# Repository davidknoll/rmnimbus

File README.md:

Projects and tools I've made while tinkering with the RM Nimbus PC-186 & PC-386
===============================================================================

Unless otherwise stated, anything here that was made by me can be used/distributed/etc under the MIT license, and none of it is approved or endorsed by [RM plc](https://www.rm.com/).

* ***8087repro*** - Reproduction of the 8087 option board for the PC-186, using a DS1100 delay line IC instead of EP8274. Prototype PCB passes basic testing.
* ***idecf*** - Ideas for how to attach a CF card to the PC-386, which uses the MCA bus so the right hardware can be harder to find.
* ***joysticksplitter*** - Allows two Atari/Commodore joysticks to be connected, as mentioned in sections 2.5.5 and 2.16.4 of the Service Manual. Two buttons are supported per joystick on pins 6 and 9, with power on pin 7. Not yet built/tested.
* ***nimbuscd*** - This contains some experiments with using a SCSI CD-ROM drive (initially, emulated with BlueSCSI) on the PC-186 with original DCB. I'm hoping to make it into `nimbuscd.sys`, a CD-ROM device driver to use with MSCDEX.
* ***nimbusmouse*** - I saw [this PS/2 mouse adaptor](https://www.thenimbus.co.uk/upgrades-and-maintenance/ps2mouse) and thought it could be done with a smaller microcontroller (specifically, an ATtiny2313 using [ATTinyCore](https://github.com/SpenceKonde/ATTinyCore)).
  * My version isn't working at the moment, but I've had aspects of it working. Work in progress.
* ***nimbusrtc*** - Attach a DS12C887A RTC pretty much directly to the bus as an expansion card.
  * This and similar RTCs are made for a multiplexed bus, so no extra latches and buffers are necessary. But because the Nimbus I/O bus is just half of a 16-bit bus, it only sees accesses where A0 is 0. The bus is shifted by one bit to make sure A0 can be 0 and the RTC registers can all still be accessed. The shift is reversed in software.
  * Not all of the RTC's RAM is accessible due to the available address space in one slot. Only chip selects 0, 2 and 4 can be used, as we also need to make sure A7 is 0 to address the right half of the RTC. Chip select 0 and interrupt 0 are generally reserved for the disk controller. An interrupt is unnecessary for the RTC if only using simple get/set commands.
  * There is a device driver that can be loaded from CONFIG.SYS to use the RTC on startup and with the TIME and DATE commands.
  * Alternatively, the get/set commands provided can be compiled on the Nimbus itself using Microsoft QuickC under SETPC. They default to expecting the RTC in slot 4, but this can be set with a switch ```/0``` - ```/4```.
* ***PC-386 RAM*** - Incomplete attempts at reproducing a decent size memory module for the PC-386.
* ***Piconet transceiver*** - Facilitates connecting a microcontroller to Piconet. Prototype PCBs so far untested- suspected pinout problem.
* ***piexpansion*** - Put a Raspberry Pi Pico W with an SD card on the PC-186 expansion bus, to hopefully emulate any physical expansion card, even the disk controller. Prototype PCB passes basic testing.
* ***reink*** - Generate block 0 for SCSI disks of any geometry, so you're not restricted to the few models in HDFORM.
  * This doesn't write the sector to the disk itself, as I don't have access to the system programmer's manual that would probably tell me how to do that. The sector is written to stdout instead, and you'll need to write it to the disk separately. (Which is made a whole lot simpler if using a SCSI2SD.)
  * You then need to run STAMP and/or HARDDISK on the Nimbus to partition the disk. I found a 64MB limit on DOS partition size, with only one DOS partition supported per disk.
  * This is not a replacement for an actual low-level format if you need one.
* ***simmadaptor*** - Adaptors for 30 or 72 pin SIMMs on the 186. Not yet tested, prototype PCBs ordered.
* ***ymplay*** - Play YM chiptune audio files using the AY-3-8910 in the Nimbus.

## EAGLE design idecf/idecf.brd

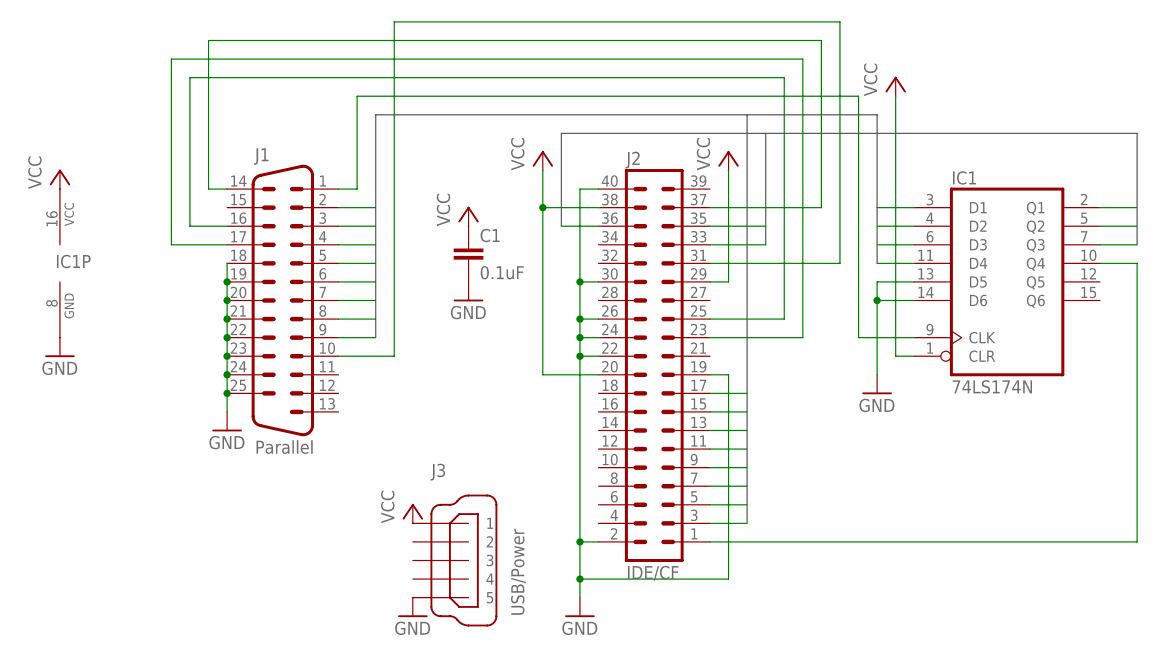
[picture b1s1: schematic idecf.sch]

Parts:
C1: 0.1uF; C050-024X044
IC1: 74LS174N; DIL16
J1: Parallel; M25HP
J2: IDE/CF; MA20-2W
J3: USB/Power; 32005-201

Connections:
!CS0: J1.14, J2.37
!RD: J1.16, J2.25
!RESET: IC1.10 (Q4), J2.1
!WR: J1.17, J2.23
A0: IC1.2 (Q1), J2.35
A1: IC1.5 (Q2), J2.33
A2: IC1.7 (Q3), J2.36
ALE: IC1.9 (CLK), J1.1
D0: IC1.3 (D1), J1.2, J2.17
D1: IC1.4 (D2), J1.3, J2.15
D2: IC1.6 (D3), J1.4, J2.13
D3: IC1.11 (D4), J1.5, J2.11
D4: J1.6, J2.9
D5: J1.7, J2.7
D6: J1.8, J2.5
D7: J1.9, J2.3
GND: C1.2, IC1.8 (GND), IC1.13 (D5), IC1.14 (D6), J1.18, J1.19, J1.20, J1.21, J1.22, J1.23, J1.24, J1.25, J2.2, J2.19, J2.22, J2.24, J2.26, J2.30, J2.40, J3.5
IRQ: J1.10, J2.31
VCC: C1.1, IC1.1 (CLR), IC1.16 (VCC), J2.20, J2.29, J2.38, J3.1

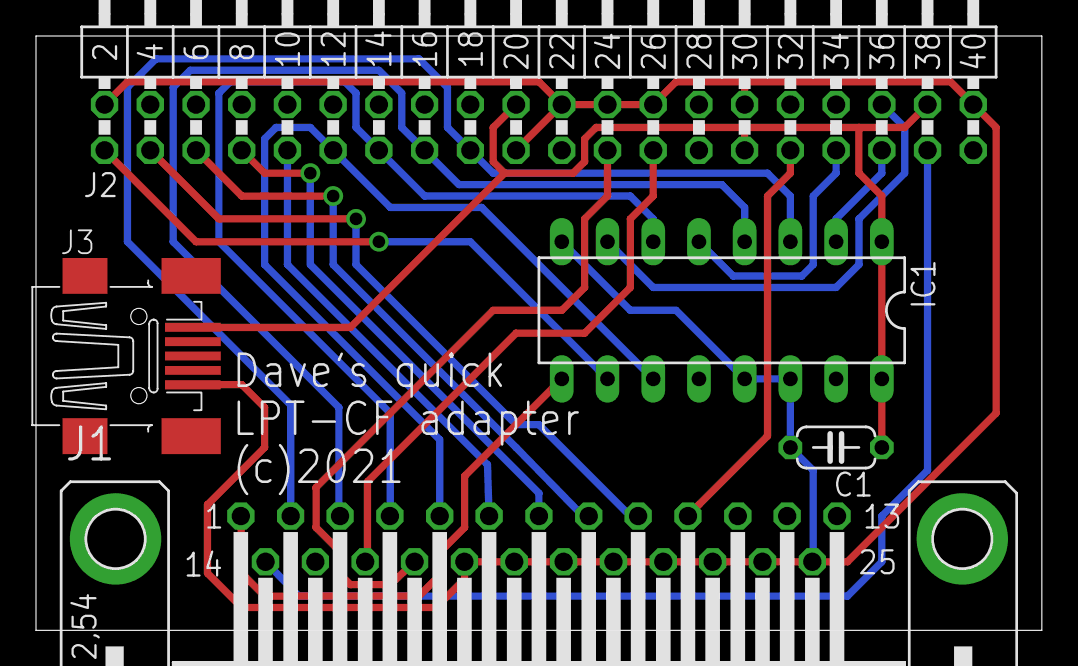
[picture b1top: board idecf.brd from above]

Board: 2 copper layers, 55.9 x 33.0 mm, 5 parts (0 on the bottom side), 19 nets.

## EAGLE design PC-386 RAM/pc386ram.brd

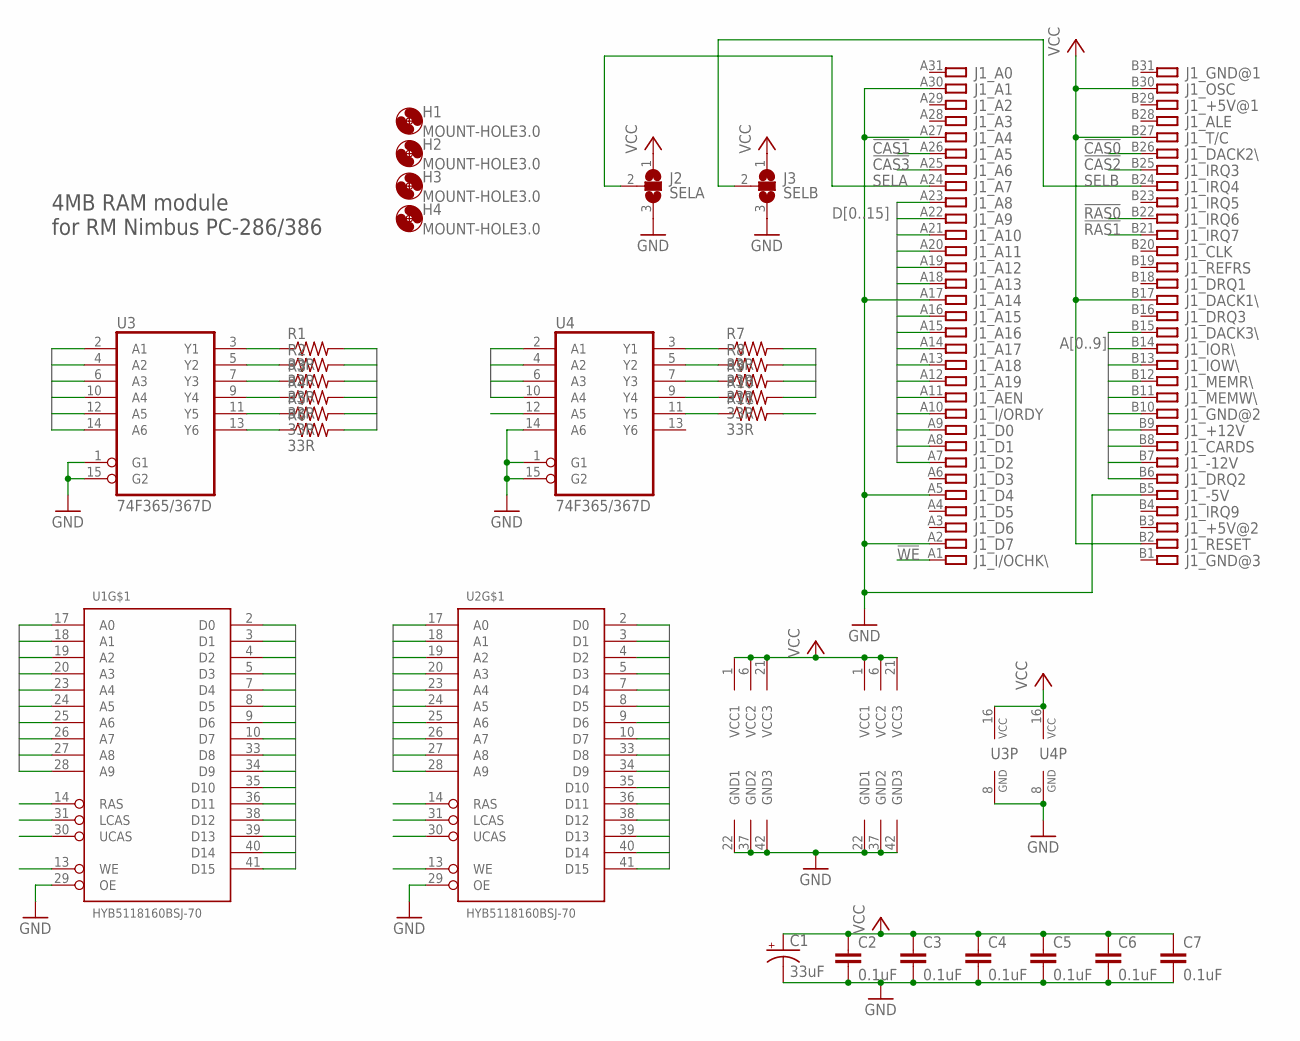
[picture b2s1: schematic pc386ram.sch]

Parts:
C1: 33uF; E2,5-7
C2, C3, C4, C5, C6, C7: 0.1uF; C050-024X044
H1, H2, H3, H4: MOUNT-HOLE3.0; 3,0
J1: PC-386 RAM slot; IBM8BIT
J2: SELA; SJ_2
J3: SELB; SJ_2
R1, R2, R3, R4, R5, R6, R7, R8, R9, R10, R11: 33R; 0204/7
U1, U2: HYB5118160BSJ-70; SOJ-42
U3, U4: 74F365/367D; SO16

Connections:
!CAS0: J1.B26, U1.30 (UCAS)
!CAS1: J1.A26, U1.31 (LCAS)
!CAS2: J1.B25, U2.30 (UCAS)
!CAS3: J1.A25, U2.31 (LCAS)
!RAS0: J1.B22, U1.14 (RAS)
!RAS1: J1.B21, U2.14 (RAS)
!WE: J1.A1, U4.12 (A5)
A0: J1.B6, U3.2 (A1)
A1: J1.B7, U3.4 (A2)
A2: J1.B8, U3.6 (A3)
A3: J1.B9, U3.10 (A4)
A4: J1.B10, U3.12 (A5)
A5: J1.B11, U3.14 (A6)
A6: J1.B12, U4.2 (A1)
A7: J1.B13, U4.4 (A2)
A8: J1.B14, U4.6 (A3)
A9: J1.B15, U4.10 (A4)
B!WE: R11.1, U4.11 (Y5)
BA0: R1.1, U3.3 (Y1)
BA1: R2.1, U3.5 (Y2)
BA2: R3.1, U3.7 (Y3)
BA3: R4.1, U3.9 (Y4)
BA4: R5.1, U3.11 (Y5)
BA5: R6.1, U3.13 (Y6)
BA6: R7.1, U4.3 (Y1)
BA7: R8.1, U4.5 (Y2)
BA8: R9.1, U4.7 (Y3)
BA9: R10.1, U4.9 (Y4)
D0: J1.A7, U1.2 (D0), U2.2 (D0)
D1: J1.A8, U1.3 (D1), U2.3 (D1)
D2: J1.A9, U1.4 (D2), U2.4 (D2)
D3: J1.A10, U1.5 (D3), U2.5 (D3)
D4: J1.A11, U1.7 (D4), U2.7 (D4)
D5: J1.A12, U1.8 (D5), U2.8 (D5)
D6: J1.A13, U1.9 (D6), U2.9 (D6)
D7: J1.A14, U1.10 (D7), U2.10 (D7)
D8: J1.A15, U1.33 (D8), U2.33 (D8)
D9: J1.A16, U1.34 (D9), U2.34 (D9)
D10: J1.A18, U1.35 (D10), U2.35 (D10)
D11: J1.A19, U1.36 (D11), U2.36 (D11)
D12: J1.A20, U1.38 (D12), U2.38 (D12)
D13: J1.A21, U1.39 (D13), U2.39 (D13)
D14: J1.A22, U1.40 (D14), U2.40 (D14)
D15: J1.A23, U1.41 (D15), U2.41 (D15)
GND: C1.-, C2.2, C3.2, C4.2, C5.2, C6.2, C7.2, J1.A2, J1.A5, J1.A17, J1.A27, J1.A30, J1.B5, J2.3, J3.3, U1.22 (GND1), U1.29 (OE), U1.37 (GND2), U1.42 (GND3), U2.22 (GND1), U2.29 (OE), U2.37 (GND2), U2.42 (GND3), U3.1 (G1), U3.8 (GND), U3.15 (G2), U4.1 (G1), U4.8 (GND), U4.14 (A6), U4.15 (G2)
M!WE: R11.2, U1.13 (WE), U2.13 (WE)
MA0: R1.2, U1.17 (A0), U2.17 (A0)
MA1: R2.2, U1.18 (A1), U2.18 (A1)
MA2: R3.2, U1.19 (A2), U2.19 (A2)
MA3: R4.2, U1.20 (A3), U2.20 (A3)
MA4: R5.2, U1.23 (A4), U2.23 (A4)
MA5: R6.2, U1.24 (A5), U2.24 (A5)
MA6: R7.2, U1.25 (A6), U2.25 (A6)
MA7: R8.2, U1.26 (A7), U2.26 (A7)
MA8: R9.2, U1.27 (A8), U2.27 (A8)
MA9: R10.2, U1.28 (A9), U2.28 (A9)
SELA: J1.A24, J2.2
SELB: J1.B24, J3.2
VCC: C1.+, C2.1, C3.1, C4.1, C5.1, C6.1, C7.1, J1.B2, J1.B17, J1.B27, J1.B30, J2.1, J3.1, U1.1 (VCC1), U1.6 (VCC2), U1.21 (VCC3), U2.1 (VCC1), U2.6 (VCC2), U2.21 (VCC3), U3.16 (VCC), U4.16 (VCC)

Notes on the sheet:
4MB RAM module for RM Nimbus PC-286/386

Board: 2 copper layers, 29 parts (0 on the bottom side), 59 nets, no tracks yet.

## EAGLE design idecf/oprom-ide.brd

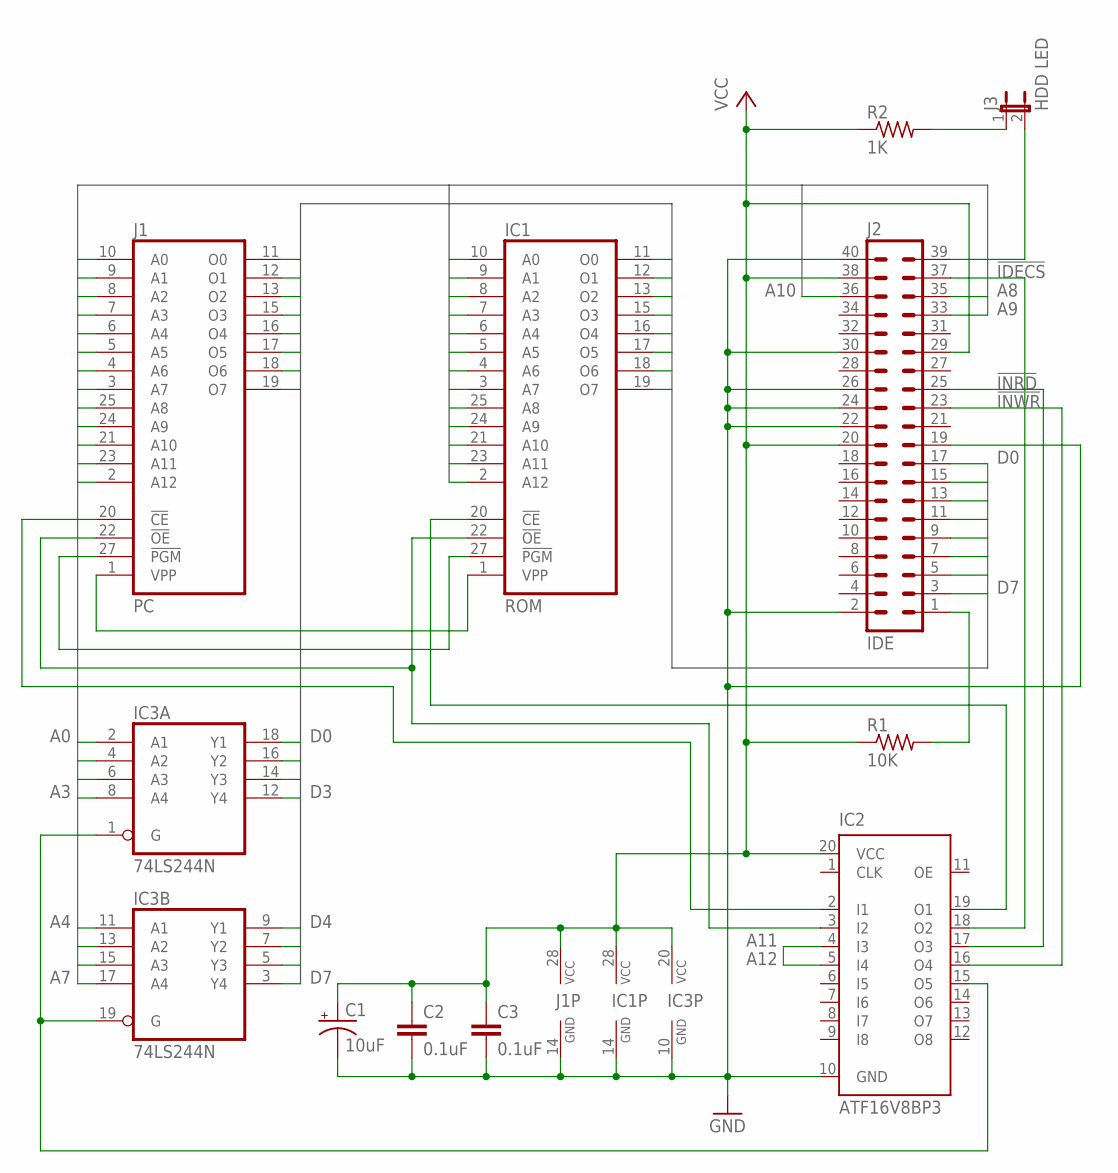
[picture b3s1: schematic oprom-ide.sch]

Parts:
C1: 10uF; E2,5-6
C2, C3: 0.1uF; C050-024X044
IC1: ROM; DIL28
IC2: ATF16V8BP3; DIL20
IC3: 74LS244N; DIL20
J1: PC; DIL28
J2: IDE; MA20-2W
J3: HDD LED; JP1
R1: 10K; 0204/7
R2: 1K; 0204/7

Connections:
!ATOD: IC2.15 (O5), IC3.1 (G), IC3.19 (G)
!EXCS: IC2.2 (I1), J1.20 (!CE)
!EXRD: IC1.22 (!OE), IC2.3 (I2), J1.22 (!OE)
!EXWR: IC1.27 (!PGM), J1.27 (!PGM)
!IDECS: IC2.18 (O2), J2.37
!IDELED: J2.39, J3.2
!INRD: IC2.17 (O3), J2.25
!INWR: IC2.16 (O4), J2.23
!RESET: J2.1, R1.2
!ROMCS: IC1.20 (!CE), IC2.19 (O1)
A0: IC1.10 (A0), IC3.2 (A1), J1.10 (A0)
A1: IC1.9 (A1), IC3.4 (A2), J1.9 (A1)
A2: IC1.8 (A2), IC3.6 (A3), J1.8 (A2)
A3: IC1.7 (A3), IC3.8 (A4), J1.7 (A3)
A4: IC1.6 (A4), IC3.11 (A1), J1.6 (A4)
A5: IC1.5 (A5), IC3.13 (A2), J1.5 (A5)
A6: IC1.4 (A6), IC3.15 (A3), J1.4 (A6)
A7: IC1.3 (A7), IC3.17 (A4), J1.3 (A7)
A8: IC1.25 (A8), J1.25 (A8), J2.35
A9: IC1.24 (A9), J1.24 (A9), J2.33
A10: IC1.21 (A10), J1.21 (A10), J2.36
A11: IC1.23 (A11), IC2.4 (I3), J1.23 (A11)
A12: IC1.2 (A12), IC2.5 (I4), J1.2 (A12)
D0: IC1.11 (O0), IC3.18 (Y1), J1.11 (O0), J2.17
D1: IC1.12 (O1), IC3.16 (Y2), J1.12 (O1), J2.15
D2: IC1.13 (O2), IC3.14 (Y3), J1.13 (O2), J2.13
D3: IC1.15 (O3), IC3.12 (Y4), J1.15 (O3), J2.11
D4: IC1.16 (O4), IC3.9 (Y1), J1.16 (O4), J2.9
D5: IC1.17 (O5), IC3.7 (Y2), J1.17 (O5), J2.7
D6: IC1.18 (O6), IC3.5 (Y3), J1.18 (O6), J2.5
D7: IC1.19 (O7), IC3.3 (Y4), J1.19 (O7), J2.3
GND: C1.-, C2.2, C3.2, IC1.14 (GND), IC2.10 (GND), IC3.10 (GND), J1.14 (GND), J2.2, J2.19, J2.22, J2.24, J2.26, J2.30, J2.40
IDELEDP: J3.1, R2.2
VCC: C1.+, C2.1, C3.1, IC1.28 (VCC), IC2.20 (VCC), IC3.20 (VCC), J1.28 (VCC), J2.20, J2.29, J2.38, R1.1, R2.1
VPP: IC1.1 (VPP), J1.1 (VPP)

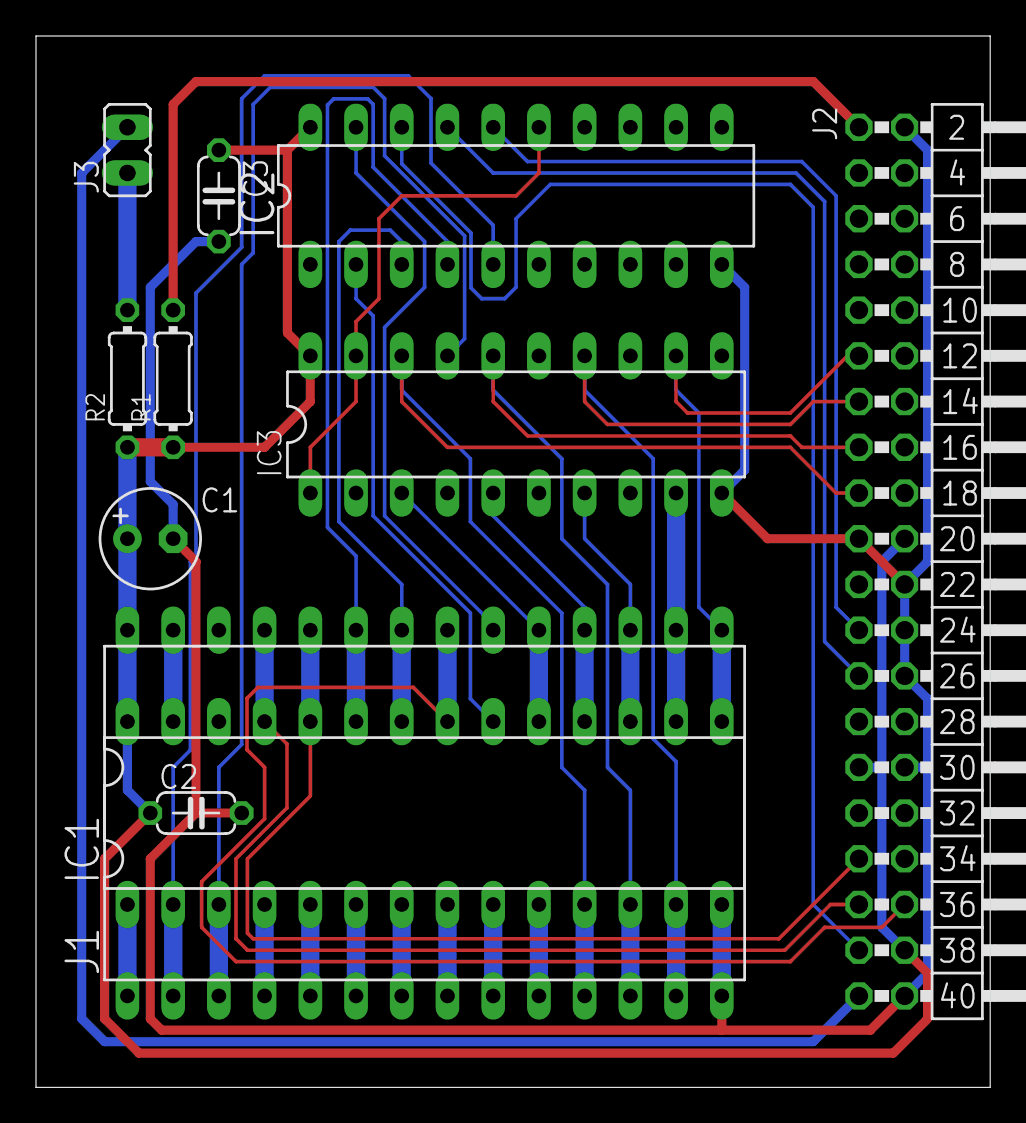
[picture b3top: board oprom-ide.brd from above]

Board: 2 copper layers, 53.0 x 58.4 mm, 11 parts (0 on the bottom side), 35 nets.

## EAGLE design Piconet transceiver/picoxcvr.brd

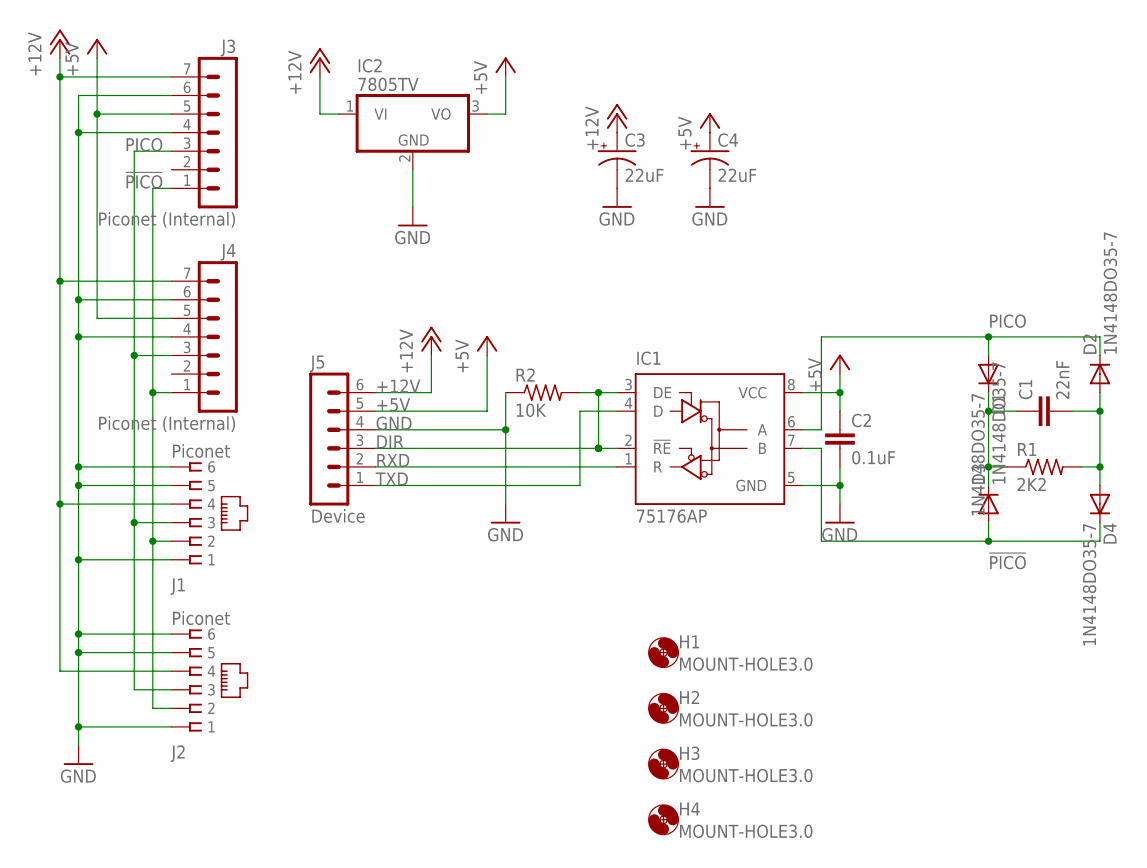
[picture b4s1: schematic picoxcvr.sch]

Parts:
C1: 22nF; C050-024X044
C2: 0.1uF; C050-024X044
C3, C4: 22uF; E2,5-6
D1, D2, D3, D4: 1N4148DO35-7; DO35-7
H1, H2, H3, H4: MOUNT-HOLE3.0; 3,0
IC1: 75176AP; DIL08
IC2: 7805TV; TO220V
J1, J2: Piconet; RJ11-NO_SHIELD
J3, J4: Piconet (Internal); MA07-1
J5: Device; MA06-1
R1: 2K2; 0204/7
R2: 10K; 0204/7

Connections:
!PICO: D3.A, D4.C, IC1.7 (B), J1.2, J2.2, J3.1, J4.1
+5V: C2.1, C4.+, IC1.8 (VCC), IC2.3 (VO), J3.5, J4.5, J5.5
+12V: C3.+, IC2.1 (VI), J1.4, J2.4, J3.7, J4.7, J5.6
DIR: IC1.2 (!RE), IC1.3 (DE), J5.3, R2.2
GND: C2.2, C3.-, C4.-, IC1.5 (GND), IC2.2 (GND), J1.1, J1.5, J1.6, J2.1, J2.5, J2.6, J3.4, J3.6, J4.4, J4.6, J5.4, R2.1
unnamed: C1.1, D1.C, D3.C, R1.1
unnamed: C1.2, D2.A, D4.A, R1.2
PICO: D1.A, D2.C, IC1.6 (A), J1.3, J2.3, J3.3, J4.3
RXD: IC1.1 (R), J5.2
TXD: IC1.4 (D), J5.1

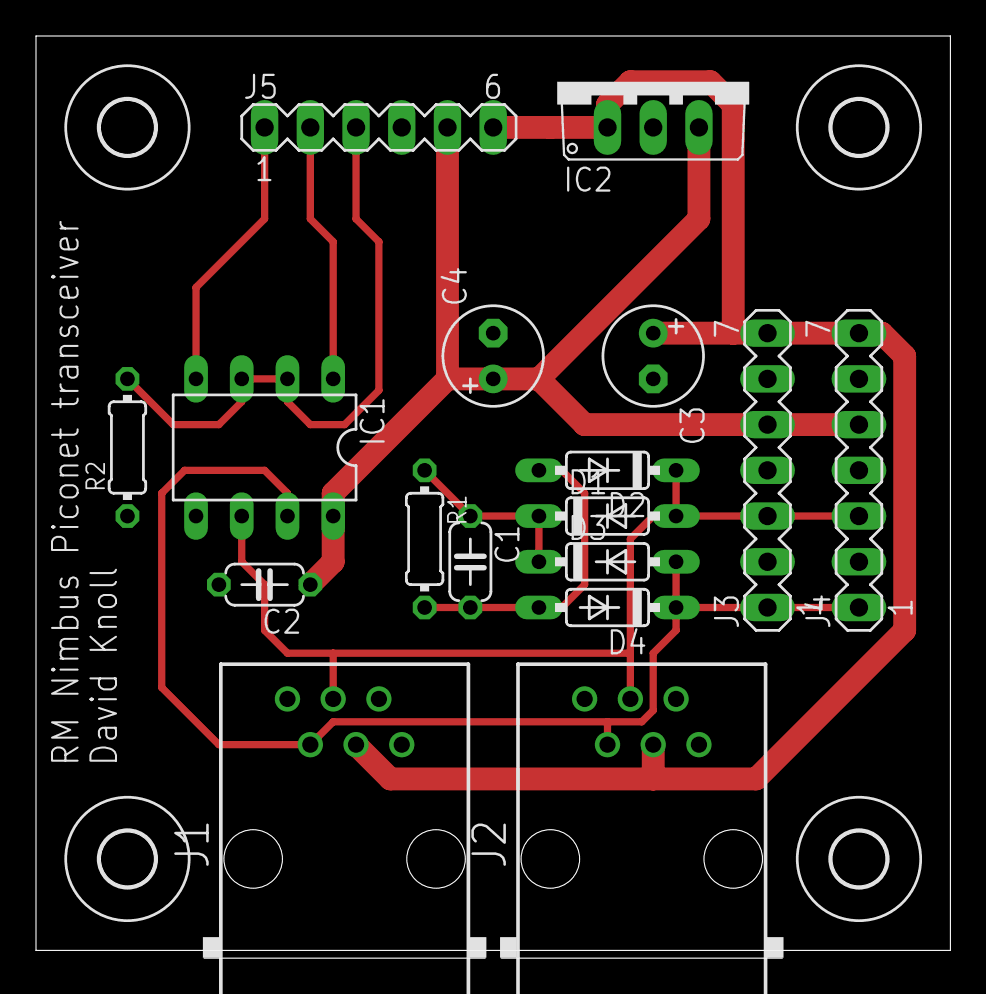
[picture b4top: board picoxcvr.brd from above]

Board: 2 copper layers, 50.8 x 51.2 mm, 21 parts (0 on the bottom side), 10 nets.

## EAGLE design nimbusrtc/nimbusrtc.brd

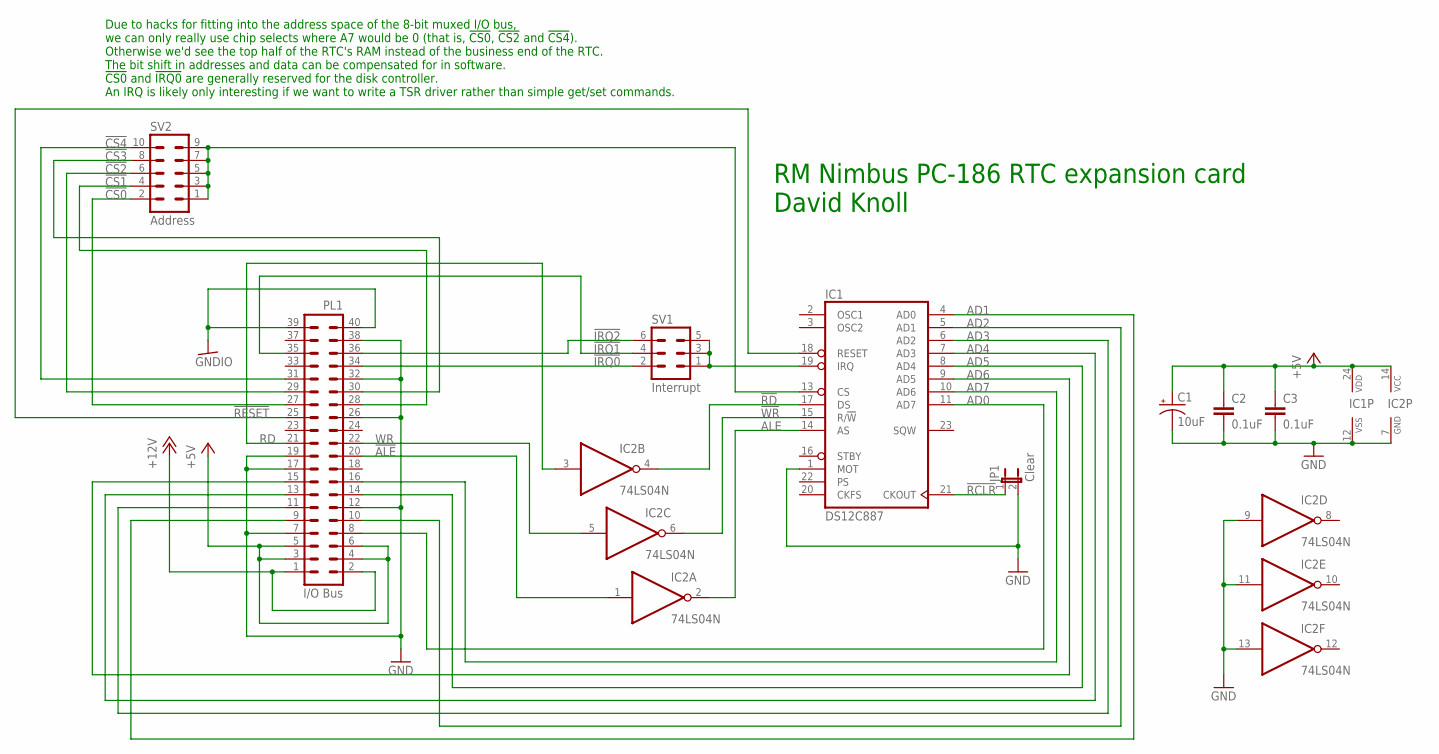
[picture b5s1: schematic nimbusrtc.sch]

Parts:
C1: 10uF; E2,5-6
C2, C3: 0.1uF; C050-024X044
IC1: DS12C887; DIL24
IC2: 74LS04N; DIL14
JP1: Clear; JP1
PL1: I/O Bus; 40H
SV1: Interrupt; MA03-2
SV2: Address; MA05-2

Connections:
!ALE: IC2.1 (I), PL1.20
!CS: IC1.13 (CS), SV2.1, SV2.3, SV2.5, SV2.7, SV2.9
!CS0: PL1.27, SV2.2
!CS1: PL1.28, SV2.4
!CS2: PL1.29, SV2.6
!CS3: PL1.30, SV2.8
!CS4: PL1.31, SV2.10
!IRQ: IC1.19 (IRQ), SV1.1, SV1.3, SV1.5
!IRQ0: PL1.34, SV1.2
!IRQ1: PL1.35, SV1.4
!IRQ2: PL1.36, SV1.6
!RCLR: IC1.21 (CKOUT), JP1.1
!RD: IC1.17 (DS), IC2.4 (O)
!RESET: IC1.18 (RESET), PL1.25
!WR: IC1.15 (R/!W), IC2.6 (O)
+5V: C1.+, C2.1, C3.1, IC1.24 (VDD), IC2.14 (VCC), PL1.3, PL1.4, PL1.5, PL1.6
+12V: PL1.1, PL1.2
AD0: IC1.11 (AD7), PL1.8
AD1: IC1.4 (AD0), PL1.9
AD2: IC1.5 (AD1), PL1.10
AD3: IC1.6 (AD2), PL1.11
AD4: IC1.7 (AD3), PL1.13
AD5: IC1.8 (AD4), PL1.14
AD6: IC1.9 (AD5), PL1.15
AD7: IC1.10 (AD6), PL1.16
ALE: IC1.14 (AS), IC2.2 (O)
GND: C1.-, C2.2, C3.2, IC1.1 (MOT), IC1.12 (VSS), IC2.7 (GND), IC2.9 (I), IC2.11 (I), IC2.13 (I), JP1.2, PL1.7, PL1.12, PL1.17, PL1.19, PL1.26, PL1.32, PL1.38
GNDIO: PL1.39, PL1.40
RD: IC2.3 (I), PL1.21
WR: IC2.5 (I), PL1.22

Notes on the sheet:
Due to hacks for fitting into the address space of the 8-bit muxed I/O bus, we can only really use chip selects where A7 would be 0 (that is, !CS0!, !CS2! and !CS4!). Otherwise we'd see the top half of the RTC's RAM instead of the business end of the RTC. The bit shift in addresses and data can be 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
RM Nimbus PC-186 RTC expansion card David Knoll

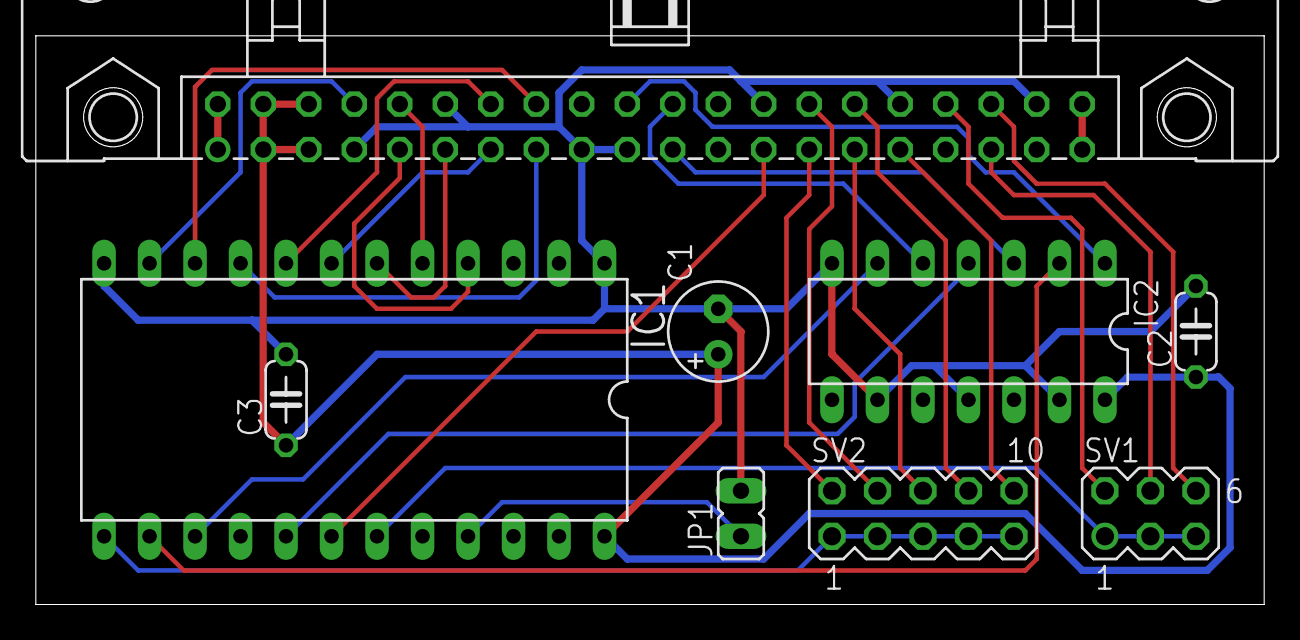
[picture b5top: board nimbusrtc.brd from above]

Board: 2 copper layers, 68.6 x 31.8 mm, 9 parts (0 on the bottom side), 30 nets.

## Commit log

2021-09-09 Add stuff
2021-09-13 Add support for different slots and modes
2022-08-18 A whole bunch
2022-09-04 Test for some key parts of the I/O board
2022-09-08 test receiving data from the bus
2022-09-10 Working emulation of my RTC board, auto set over WiFi
2022-09-22 reorganisation
2022-09-23 Test IRQs on device emulator
2022-10-21 Attempt at emulating parallel printer card, not working probably due to something with interrupts / acknowledge signal
2022-10-26 Emulate the DCC card
    Seems to work for Kermit, including the rx interrupt, but fails DCCPT
    badly because I don't emulate the test jig. Also doesn't emulate DMA.
2022-10-31 DCC: DMA (not tested), improve debug messages
2022-11-01 Multiple devices coexisting
2023-02-13 Experiment with accessing a SCSI CD-ROM
2023-02-15 nimbuscd: add inquiry test, add timeouts
2023-02-24 first test version of cd driver, mscdex freezes
2023-02-25 A command to probe devices on the Nimbus SASI bus
2023-02-25 preliminary untested fdc emulation, left disabled
2023-03-28 Design a joystick splitter
2023-03-28 Add skeleton CD write function, emulate DCC B for future use
2024-11-28 Add CLOCK$ device driver for Dallas RTC
2024-12-04 Fix bug in RTC driver when card not present, more features for the Pico RTC emulation, Bluetooth debug channel
2025-01-11 wip sasi emulation bits that also arent tested
2025-01-13 begin to c++ify the card slots, add periodic interrupt support to rtc
2025-01-13 c++ify the parallel device
2025-01-14 c++ify the dcc device
2025-01-14 reset and device slots stuff
2025-01-14 rename some files
2025-02-10 SIMM adaptors for the 186
2025-03-11 YM audio player
2025-03-11 Tolerate but don't implement YM6, digidrums, and additional data
2025-03-12 Minor corrections
2025-03-15 Support more formats
2025-03-15 indicate compressed files
2025-05-17 Reorganise some stuff, add the multi device and its driver
    Although the RTC examples seem to work, there is some spurious/incorrect data when emulating a character device- possibly PIO, possibly hardware/logic level?

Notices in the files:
idecf/idecf.brd:
(c)2021
